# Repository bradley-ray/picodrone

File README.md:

# Pico Quadcopter Drone

- `hardware/` contains the kicad schematic and pcb layout files 
    - qx95 drone frame
    - 8520 brushed motors
    - header sockets for raspberry pi pico
    - header sockets for mpu 6050 breakout board
    - header sockets for sd card spi breakout board (future use)

- `firmware/` contains the code for the microcontroller
    - requires pico_sdk to be downloaded and PICO_SDK_PATH to be set
    - uses `btstack` and bluetooth rfcomm to receive control commands over bluetooth connection

- `app/` contains python script to send inputs from ps4 controller to drone
    - install `pyPS4Controller` and `pySerial`
    - find pico_w bt addr using `sdptool browse`
    - run `rfcomm connect /dev/rfcomm0 <btaddr>` to connect to the drone
    - run `python3 main.py rfcomm0`
    - connect ps4 controller
        - `triangle` - increase pitch
        - `cross` - decrease pitch
        - `square` - roll left
        - `circle` - roll right
        - `up arrow` - increase throttle
        - `down arrow` - decrease throttle
        - `left arrow` - yaw left
        - `right arrow` - yaw right

## TODO
- need to fix value drift on imu
- need a filter or something for improved imu data
- need to continue and test and adjust pid values

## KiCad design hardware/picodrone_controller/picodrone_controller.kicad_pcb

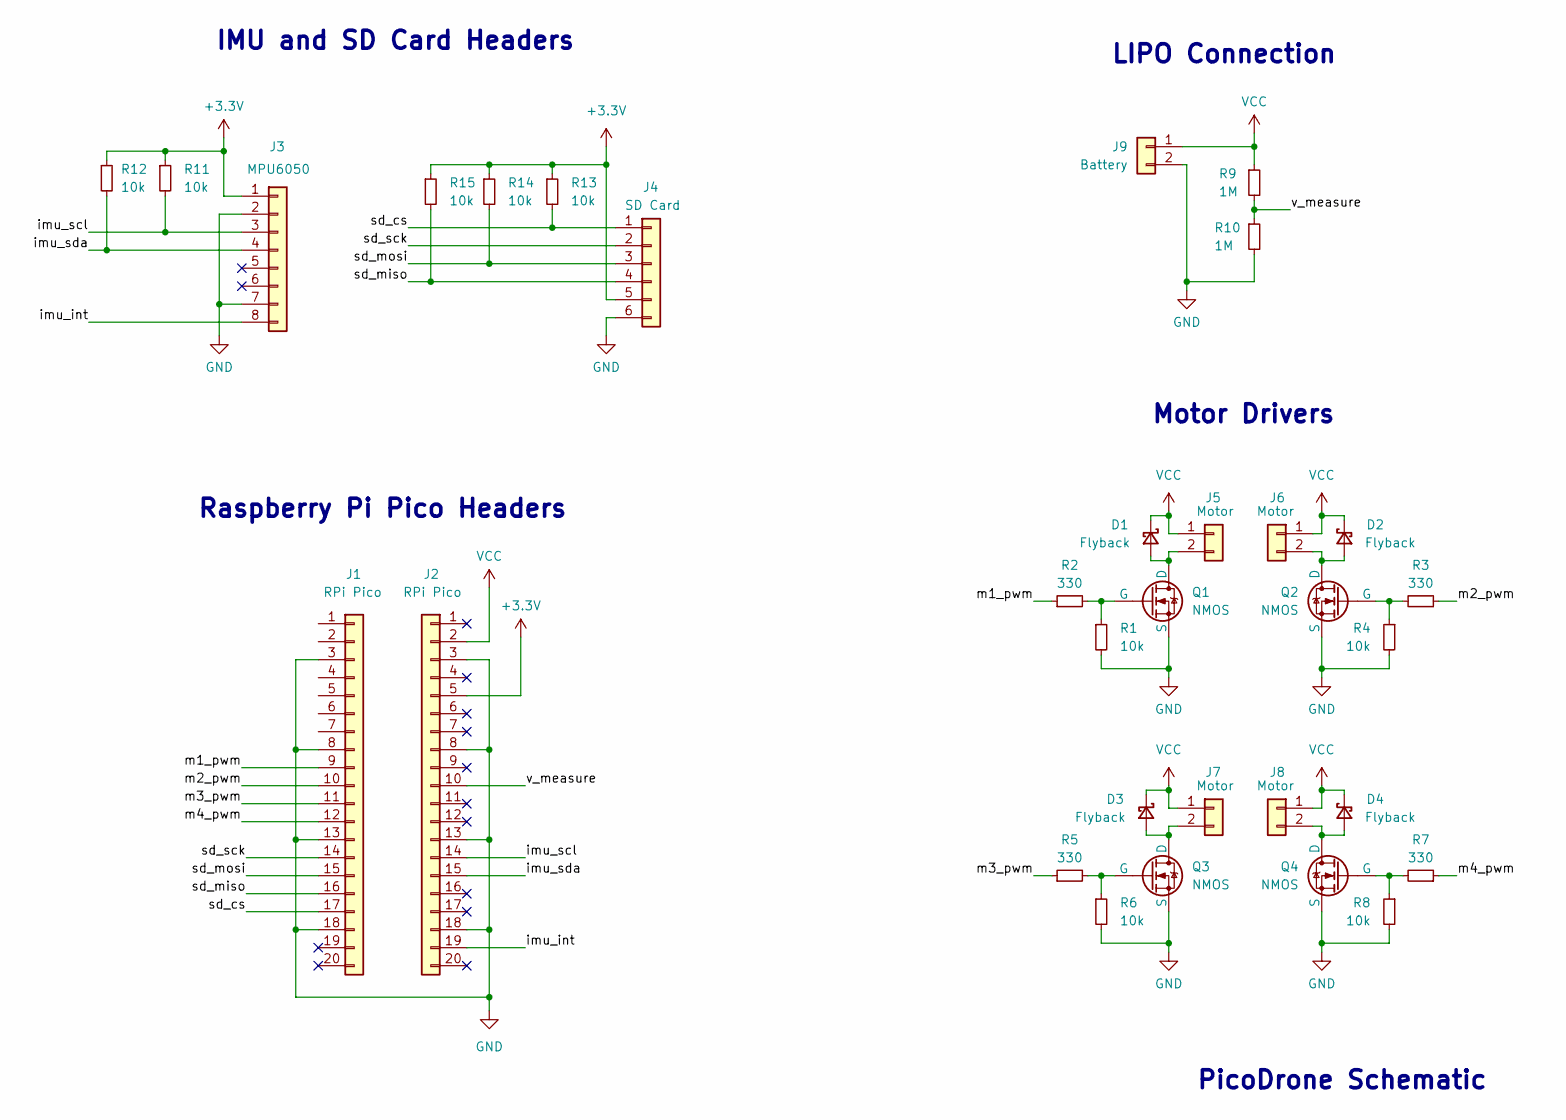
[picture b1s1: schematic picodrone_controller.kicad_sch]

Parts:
D1, D2, D3, D4: Flyback; SODFL3618X110N
J1, J2: RPi Pico; PinSocket_1x20_P2.54mm_Vertical
J3: MPU6050; PinSocket_1x08_P2.54mm_Vertical
J4: SD Card; PinSocket_1x06_P2.54mm_Vertical
J5, J6, J7, J8: Motor; PinHeader_1x02_P2.54mm_Vertical
J9: Battery; PinHeader_1x02_P2.54mm_Vertical
Q1, Q2, Q3, Q4: NMOS; TO-236_VIS
R1, R4, R6, R8, R11, R12, R13, R14, R15: 10k; R_0805_2012Metric
R2, R3, R5, R7: 330; R_0805_2012Metric
R9, R10: 1M; R_0805_2012Metric

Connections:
+3.3V: J2.5, J3.1, J4.5, R11.1, R12.1, R13.1, R14.1, R15.1
/imu_int: J2.19, J3.8
/imu_scl: J2.14, J3.3, R11.2
/imu_sda: J2.15, J3.4, R12.2
/m1_pwm: J1.9, R2.1
/m2_pwm: J1.10, R3.1
/m3_pwm: J1.11, R5.1
/m4_pwm: J1.12, R7.1
/sd_cs: J1.17, J4.1, R13.2
/sd_miso: J1.16, J4.4, R15.2
/sd_mosi: J1.15, J4.3, R14.2
/sd_sck: J1.14, J4.2
/v_measure: J2.10, R9.2, R10.1
GND: J1.3, J1.8, J1.13, J1.18, J2.3, J2.8, J2.13, J2.18, J3.2, J3.7, J4.6, J9.2, Q1.3 (S), Q2.3 (S), Q3.3 (S), Q4.3 (S), R1.2, R4.2, R6.2, R8.2, R10.2
unnamed: D1.2 (A), J5.2, Q1.1 (D)
unnamed: D2.2 (A), J6.2, Q2.1 (D)
unnamed: D3.2 (A), J7.2, Q3.1 (D)
unnamed: D4.2 (A), J8.2, Q4.1 (D)
unnamed: Q1.2 (G), R1.1, R2.2
unnamed: Q2.2 (G), R3.2, R4.1
unnamed: Q3.2 (G), R5.2, R6.1
unnamed: Q4.2 (G), R7.2, R8.1
VCC: D1.1 (K), D2.1 (K), D3.1 (K), D4.1 (K), J2.2, J5.1, J6.1, J7.1, J8.1, J9.1, R9.1

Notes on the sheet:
Motor Drivers
Raspberry Pi Pico Headers
PicoDrone Schematic
LIPO Connection
IMU and SD Card Headers

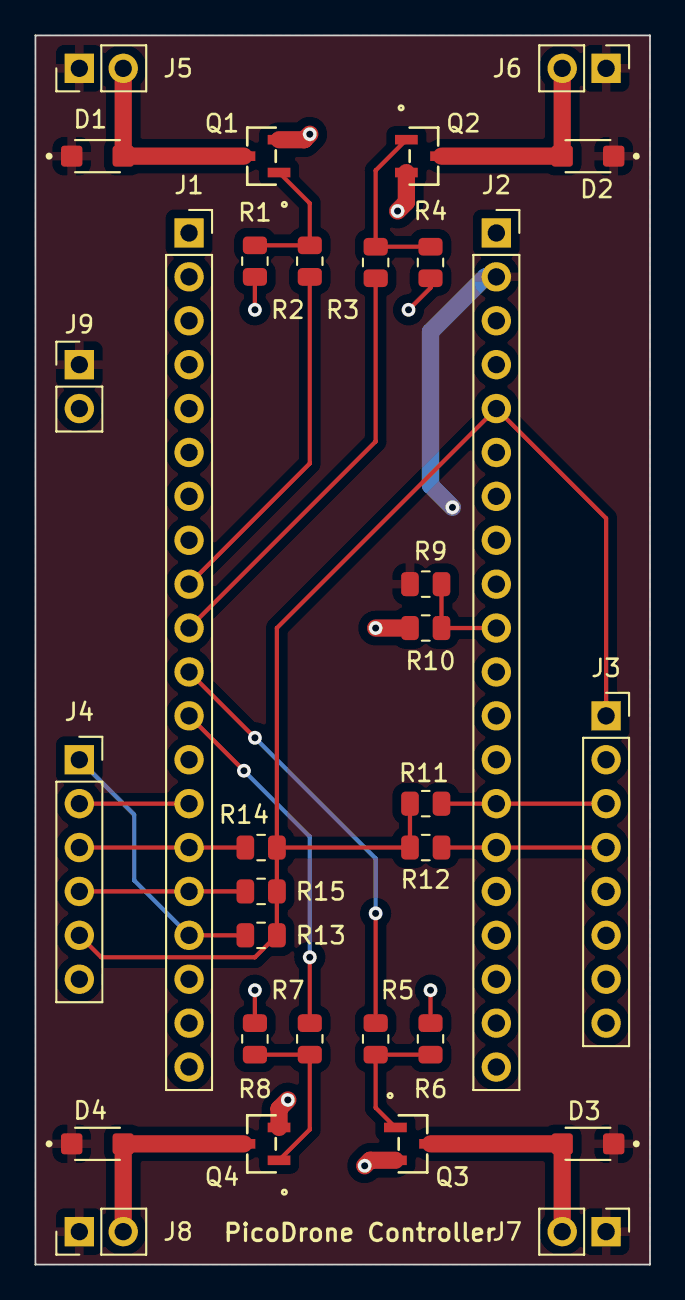
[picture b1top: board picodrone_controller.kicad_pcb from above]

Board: 2 copper layers, 35.6 x 71.1 mm, 32 parts (0 on the bottom side), 22 nets.

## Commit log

2023-07-11 initial kicad project
2023-07-12 initial schematic
2023-07-12 updated gitignore
2023-07-14 rearrange schematic to help with pcb layout
2023-07-14 initial pcb layout
2023-07-14 update README with hardware tasks
2023-07-15 generated gerbers and ordered
2023-07-29 update clearances
2023-07-29 add pcb and assembled photos
2023-07-30 add hello world to pico
2023-07-31 add freertos kernel
2023-08-02 move to no rtos, just btstack
2023-08-02 remove unused bluetooth task
2023-08-03 start mpu6050 dev
2023-08-04 test mpu with bluetooth timers
2023-08-06 implement basic control for ps4 controller
2023-08-08 starting code for motor control
2023-08-08 add lib/control to Cmake
2023-08-08 improve types
2023-08-08 orientation_t -> mpu_angles_t
2023-08-08 remove log.txt
2023-08-09 fix pinout and bt packet type casting issue
2023-08-09 update readme with current progress
2023-08-09 fix pitch, roll, yaw directions
2023-08-10 prevent startup until bluetooth connected
2023-08-10 add fully assembled picture
2023-08-10 fix readme and photo
2023-08-10 correct misinformation
